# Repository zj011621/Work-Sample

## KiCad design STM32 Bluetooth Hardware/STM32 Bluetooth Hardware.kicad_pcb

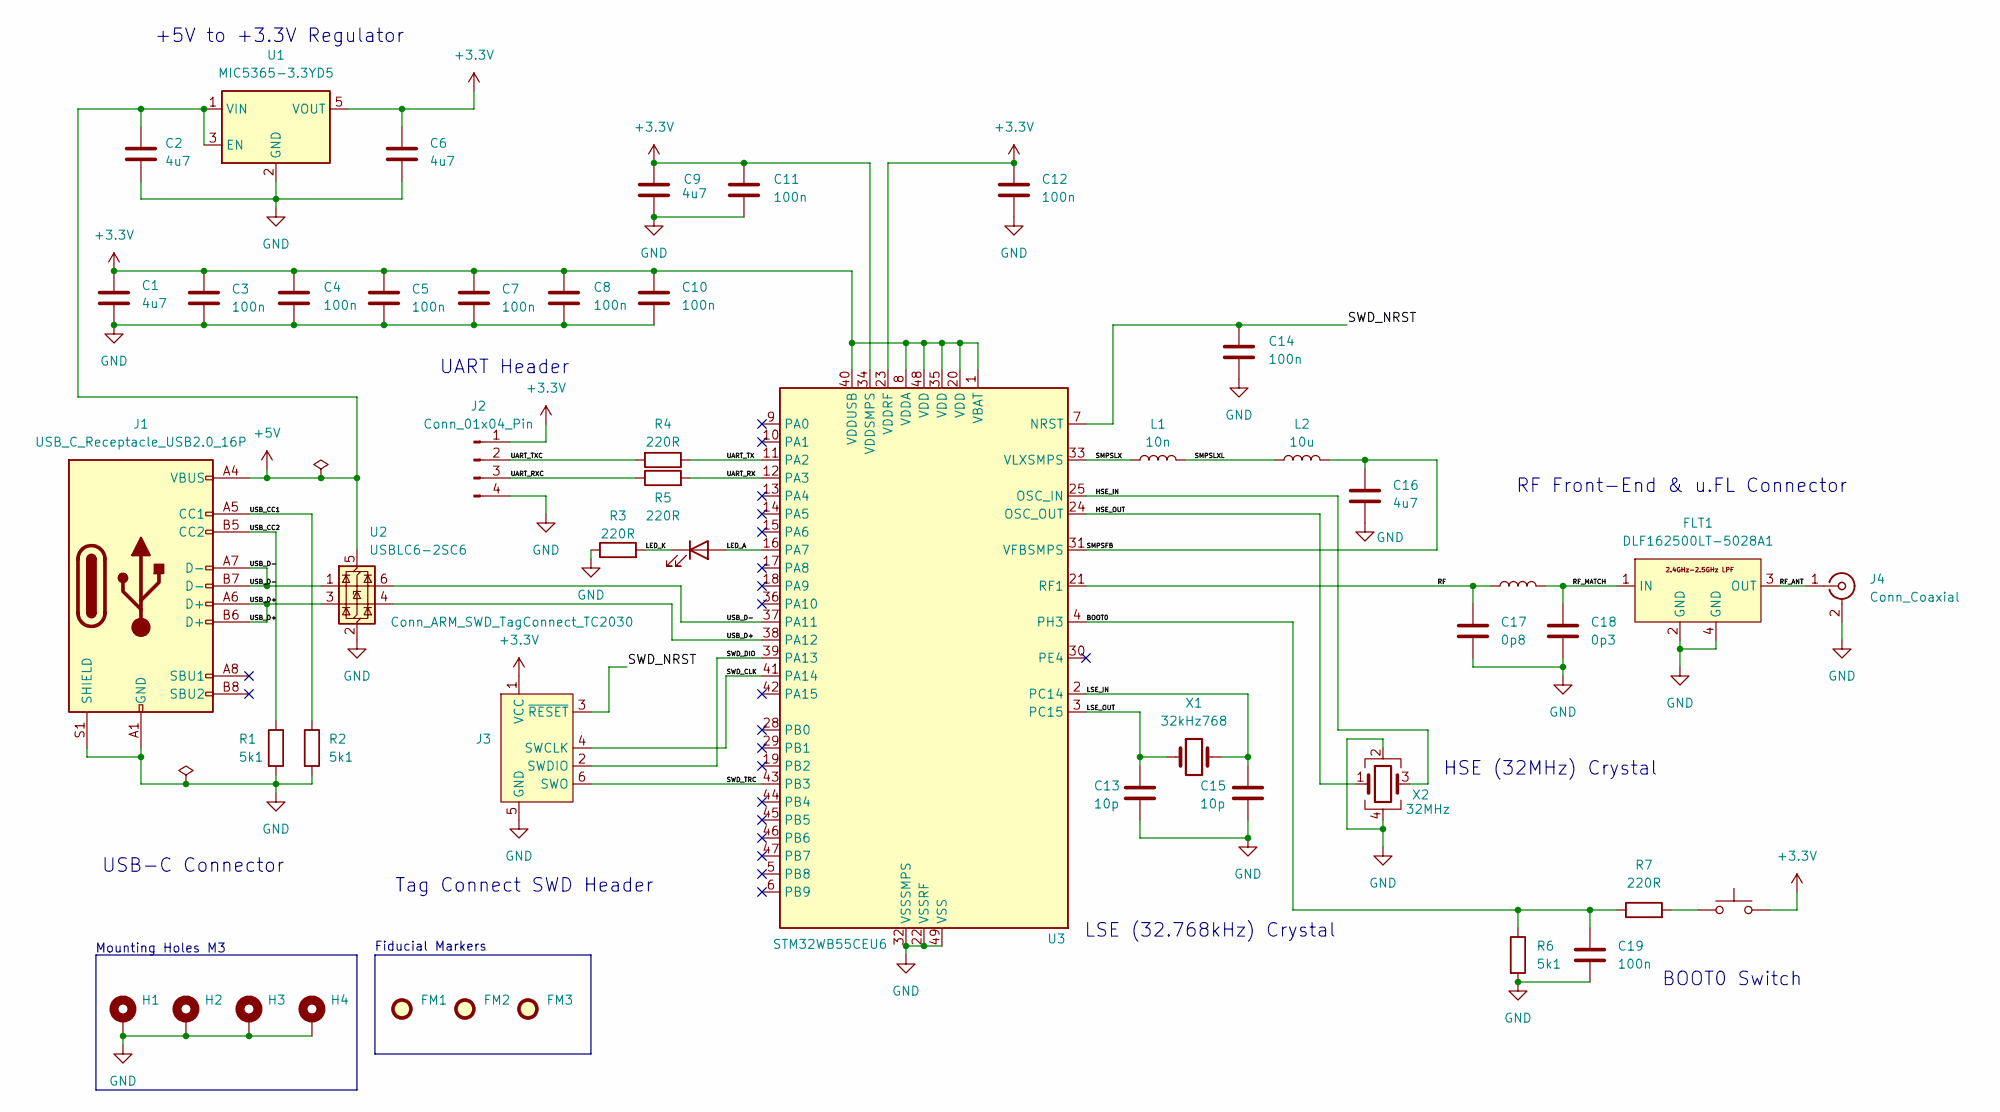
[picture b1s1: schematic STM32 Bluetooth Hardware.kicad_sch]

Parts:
C1, C2, C6, C9, C16: 4u7; C_0603_1608Metric; Manufacturer Part Number 0603YD475MAT2A
C3, C4, C5, C7, C8, C10, C11, C12, C14, C19: 100n; C_0402_1005Metric; Manufacturer Part Number 04026C104KAT2A
C13, C15: 10p; C_0402_1005Metric; Manufacturer Part Number KGM05ACG1H100JN
C17: 0p8; C_0402_1005Metric; Manufacturer Part Number GRM1555C1HR80BA01D
C18: 0p3; C_0402_1005Metric; Manufacturer Part Number GRM1555C1HR30WA01D
D1: LED; LED_0402_1005Metric; Manufacturer Part Number 150040RS73240
FLT1: DLF162500LT-5028A1; Manufacturer Part Number DLF162500LT-5028A1
FM1, FM2, FM3: Fiducial; Fiducial_1mm_Mask2mm
H1, H2, H3, H4: MountingHole_Pad; MountingHole_2.2mm_M2_Pad_Via
J1: USB_C_Receptacle_USB2.0_16P; USB_C_Receptacle_GCT_USB4105-xx-A_16P_TopMnt_Horizontal; Manufacturer Part Number USB4105-GF-A
J2: Conn_01x04_Pin; Molex_PicoBlade_53048-0410_1x04_P1.25mm_Horizontal; Manufacturer Part Number 0530480410
J3: Conn_ARM_SWD_TagConnect_TC2030; Tag-Connect_TC2030-IDC-FP_2x03_P1.27mm_Vertical
J4: Conn_Coaxial; U.FL_Hirose_U.FL-R-SMT-1_Vertical; Manufacturer Part Number U.FL-R-SMT(01)
L1: 10n; L_0402_1005Metric; Manufacturer Part Number LQG15WZ10NJ02D
L2: 10u; L_0805_2012Metric; Manufacturer Part Number LQM21FN100M80L
L3: 2n7; L_0402_1005Metric; Manufacturer Part Number LQG15HS2N7S02D
R1, R2, R6: 5k1; R_0402_1005Metric; Manufacturer Part Number RC0603FR-075K1L
R3, R4, R5, R7: 220R; R_0402_1005Metric; Manufacturer Part Number RC0402FR-07221RL
SW1: SW_Push; SW_SPST_CK_RS282G05A3; Manufacturer Part Number RS-282G05A3-SM RT
U1: MIC5365-3.3YD5; SOT-23-5; Manufacturer Part Number MIC5365-3.3YD5-TR
U2: USBLC6-2SC6; SOT-23-6; Manufacturer Part Number USBLC6-2SC6
U3: STM32WB55CEU6; QFN-48-1EP_7x7mm_P0.5mm_EP5.6x5.6mm; Manufacturer Part Number STM32WB55CEU6
X1: 32kHz768; Crystal_SMD_2012-2Pin_2.0x1.2mm; Manufacturer Part Number STDMUB1-32.768K
X2: 32MHz; Crystal_SMD_2016-4Pin_2.0x1.6mm; Manufacturer Part Number CS06465-32M

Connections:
+3.3V: C1.1, C3.1, C4.1, C5.1, C6.1, C7.1, C8.1, C9.1, C10.1, C11.1, C12.1, J2.1, J3.1 (VCC), SW1.2, U1.5 (VOUT), U3.1 (VBAT), U3.8 (VDDA), U3.20 (VDD), U3.23 (VDDRF), U3.34 (VDDSMPS), U3.35 (VDD), U3.40 (VDDUSB), U3.48 (VDD)
+5V: C2.1, J1.A4 (VBUS), J1.A9 (VBUS), J1.B4 (VBUS), J1.B9 (VBUS), U1.1 (VIN), U1.3 (EN), U2.5 (VBUS)
/BOOT0: C19.1, R6.1, R7.1, U3.4 (PH3)
/HSE_IN: U3.25 (OSC_IN), X2.3
/HSE_OUT: U3.24 (OSC_OUT), X2.1
/LED_A: D1.2 (A), U3.16 (PA7)
/LED_K: D1.1 (K), R3.2
/LSE_IN: C15.1, U3.2 (PC14), X1.2
/LSE_OUT: C13.1, U3.3 (PC15), X1.1
/RF: C17.1, L3.1, U3.21 (RF1)
/RF_ANT: FLT1.3 (OUT), J4.1 (In)
/RF_MATCH: C18.1, FLT1.1 (IN), L3.2
/SMPSFB: C16.2, L2.2, U3.31 (VFBSMPS)
/SMPSLX: L1.1, U3.33 (VLXSMPS)
/SMPSLXL: L1.2, L2.1
/SWD_CLK: J3.4 (SWCLK), U3.41 (PA14)
/SWD_DIO: J3.2 (SWDIO), U3.39 (PA13)
/SWD_NRST: C14.1, J3.3 (~RESET), U3.7 (NRST)
/SWD_TRC: J3.6 (SWO), U3.43 (PB3)
/UART_RX: R5.2, U3.12 (PA3)
/UART_RXC: J2.3, R5.1
/UART_TX: R4.1, U3.11 (PA2)
/UART_TXC: J2.2, R4.2
/USB_CC1: J1.A5 (CC1), R2.1
/USB_CC2: J1.B5 (CC2), R1.1
/USB_D+: J1.A6 (D+), J1.B6 (D+), U2.3 (I/O2), U2.4 (I/O2), U3.38 (PA12)
/USB_D-: J1.A7 (D-), J1.B7 (D-), U2.1 (I/O1), U2.6 (I/O1), U3.37 (PA11)
GND: C1.2, C2.2, C3.2, C4.2, C5.2, C6.2, C7.2, C8.2, C9.2, C10.2, C11.2, C12.2, C13.2, C14.2, C15.2, C16.1, C17.2, C18.2, C19.2, FLT1.2 (GND), FLT1.4 (GND), H1.1, H2.1, H3.1, H4.1, J1.A1 (GND), J1.A12 (GND), J1.B1 (GND), J1.B12 (GND), J1.S1 (SHIELD), J2.4, J3.5 (GND), J4.2 (Ext), R1.2, R2.2, R3.1, R6.2, U1.2 (GND), U2.2 (GND), U3.22 (VSSRF), U3.32 (VSSSMPS), U3.49 (VSS), X2.2, X2.4
unnamed: R7.2, SW1.1

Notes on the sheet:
UART Header
LSE (32.768kHz) Crystal
HSE (32MHz) Crystal
Tag Connect SWD Header
Fiducial Markers
Mounting Holes M3
BOOT0 Switch
USB-C Connector
+5V to +3.3V Regulator
RF Front-End & u.FL Connector

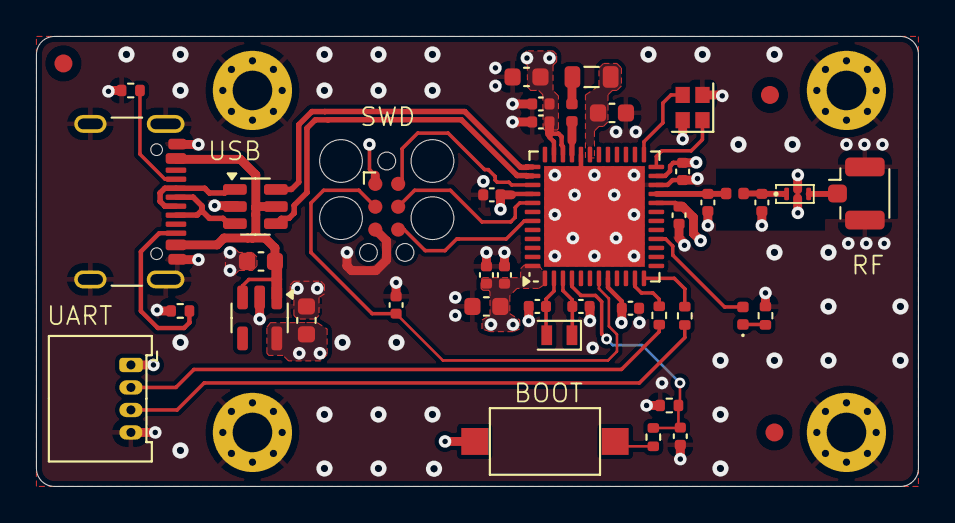
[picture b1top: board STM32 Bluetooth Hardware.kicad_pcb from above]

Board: 4 copper layers, 49.0 x 25.0 mm, 48 parts (0 on the bottom side), 29 nets.

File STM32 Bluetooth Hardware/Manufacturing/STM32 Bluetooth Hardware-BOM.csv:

"Designator","Quantity","Value","Footprint","Description","Manufacturer","Manufacturer Part Number","Distributor Link"
"C1, C2, C6, C9, C16","5","4u7","Capacitor_SMD:C_0603_1608Metric","Unpolarized capacitor","  KYOCERA AVX","  0603YD475MAT2A","https://www.digikey.com/en/products/detail/kyocera-avx/0603Y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",""
"C3, C4, C5, C7, C8, C10, C11, C12, C14, C19","10","100n","Capacitor_SMD:C_0402_1005Metric","Unpolarized capacitor","  KYOCERA AVX","  04026C104KAT2A","https://www.digikey.com/en/products/detail/kyocera-avx/04026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",""
"C13, C15","2","10p","Capacitor_SMD:C_0402_1005Metric","Unpolarized capacitor","  KYOCERA AVX","KGM05ACG1H100JN","https://www.digikey.com/en/products/detail/kyocera-avx/KGM05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",""
"C17","1","0p8","Capacitor_SMD:C_0402_1005Metric","Unpolarized capacitor","  Murata Electronics","GRM1555C1HR80BA01D","https://www.digikey.com/en/products/detail/murata-electronic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",""
"C18","1","0p3","Capacitor_SMD:C_0402_1005Metric","Unpolarized capacitor","  Murata Electronics","  GRM1555C1HR30WA01D","https://www.digikey.com/en/products/detail/murata-electronic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",""
"D1","1","LED","LED_SMD:LED_0402_1005Metric","Light emitting diode","  Würth Elektronik","  150040RS73240","https://www.digikey.com/en/products/detail/w%C3%BCrth-elektr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",""
"FLT1","1","DLF162500LT-5028A1","STM32_BH_Footprints:DLF162500LT-5028A1","","  TDK Corporation","  DLF162500LT-5028A1","https://www.digikey.com/en/products/detail/tdk-corporation/D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",""
"J1","1","USB_C_Receptacle_USB2.0_16P","STM32_BH_Footprints:USB_C_Receptacle_GCT_USB4105-xx-A_16P_TopMnt_Horizontal","USB 2.0-only 16P Type-C Receptacle connector","GCT"," USB4105-GF-A","https://www.digikey.com/en/products/detail/gct/USB4105-GF-A/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",""
"J2","1","Conn_01x04_Pin","Connector_Molex:Molex_PicoBlade_53048-0410_1x04_P1.25mm_Horizontal","Generic connector, single row, 01x04, script generated","Molex","0530480410","https://www.digikey.com/en/products/detail/molex/0530480410/242866",""
"J4","1","Conn_Coaxial","Connector_Coaxial:U.FL_Hirose_U.FL-R-SMT-1_Vertical","coaxial connector (BNC, SMA, SMB, SMC, Cinch/RCA, LEMO, ...)","  Hirose Electric Co Ltd","  U.FL-R-SMT(01)","https://www.digikey.com/en/products/detail/hirose-electric-c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",""
"L1","1","10n","Inductor_SMD:L_0402_1005Metric","Inductor","r Murata Electronics","  LQG15WZ10NJ02D","https://www.digikey.com/en/products/detail/murata-electronic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",""
"L2","1","10u","Inductor_SMD:L_0805_2012Metric","Inductor","  Murata Electronics","  LQM21FN100M80L","https://www.digikey.com/en/products/detail/murata-electronic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",""
"L3","1","2n7","Inductor_SMD:L_0402_1005Metric","Inductor","  Murata Electronics","  LQG15HS2N7S02D","https://www.digikey.com/en/products/detail/murata-electronic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",""
"R1, R2, R6","3","5k1","Resistor_SMD:R_0402_1005Metric","Resistor","  YAGEO","  RC0603FR-075K1L","https://www.digikey.com/en/products/detail/yageo/rc0603fr-07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",""
"R3, R4, R5, R7","4","220R","Resistor_SMD:R_0402_1005Metric","Resistor","  YAGEO","  RC0402FR-07221RL","https://www.digikey.com/en/products/detail/yageo/rc0402fr-07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",""
"SW1","1","SW_Push","Button_Switch_SMD:SW_SPST_CK_RS282G05A3","Push button switch, generic, two pins","  C&K","  RS-282G05A3-SM RT","https://www.digikey.com/en/products/detail/c-k/RS-282G05A3-S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",""
"U1","1","MIC5365-3.3YD5","Package_TO_SOT_SMD:SOT-23-5","150mA Low-dropout Voltage Regulator, Vout 3.3V, Vin up to 5.5V, SOT-23-5","  Microchip Technology","  MIC5365-3.3YD5-TR","https://www.digikey.com/en/products/detail/microchip-technol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",""
"U2","1","USBLC6-2SC6","Package_TO_SOT_SMD:SOT-23-6","Very low capacitance ESD protection diode, 2 data-line, SOT-23-6","  UMW","  USBLC6-2SC6","2sc6/16705896",""
"U3","1","STM32WB55CEU6","Package_DFN_QFN:QFN-48-1EP_7x7mm_P0.5mm_EP5.6x5.6mm","STMicroelectronics Arm Cortex-M4 MCU, 512KB flash, 256KB RAM, 64 MHz, 1.71-3.6V, 30 GPIO, UFQFPN48","  STMicroelectronics","STM32WB55CEU6","https://www.digikey.com/en/products/detail/stmicroelectronic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",""
"X1","1","32kHz768","Crystal:Crystal_SMD_2012-2Pin_2.0x1.2mm","Two pin crystal","  NDK (NIHON DEMPA KOGYO CO., LTD)","  STDMUB1-32.768K","https://www.digikey.com/en/products/detail/ndk-nihon-dempa-k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",""
"X2","1","32MHz","Crystal:Crystal_SMD_2016-4Pin_2.0x1.6mm","Four pin crystal, GND on pins 2 and 4","  NDK (NIHON DEMPA KOGYO CO., LTD)","CS06465-32M","https://www.digikey.com/en/products/detail/ndk-nihon-dempa-k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",""

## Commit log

2025-03-26 Create ...
2025-03-26 Create Jerky Counter
2025-03-26 Create Placeholder
2025-04-11 Create temp
